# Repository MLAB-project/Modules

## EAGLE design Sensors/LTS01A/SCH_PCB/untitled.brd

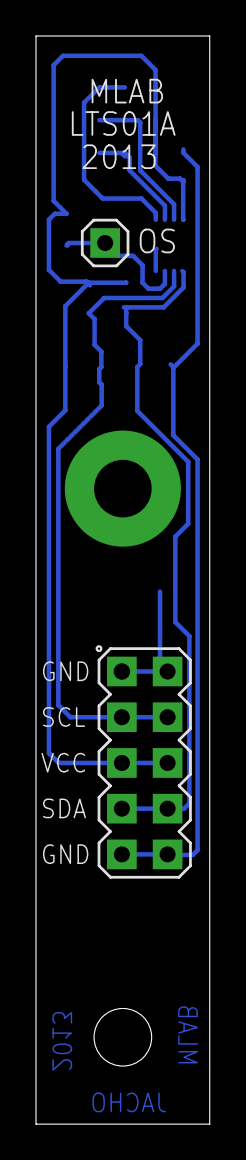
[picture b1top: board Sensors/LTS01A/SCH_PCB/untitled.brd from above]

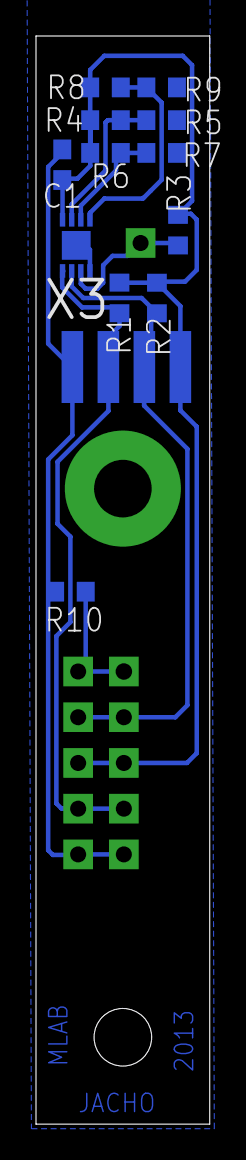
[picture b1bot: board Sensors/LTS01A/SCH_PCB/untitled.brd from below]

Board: 2 copper layers, 9.7 x 60.5 mm, 16 parts (13 on the bottom side), 9 nets.

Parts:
C1: 100nF; C0603
R1, R2, R3: 10k; R0603
R4, R5, R6, R7, R8, R9, R10: 0R; R0603
SV1: MA05-2
SV2: SMD_MA04-1
SV4: MA01-1
X2: SROUB3M
X3: TDFN8

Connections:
A0: R4.2, R5.1, X3.7
A1: R6.2, R7.1, X3.6
A2: R8.2, R9.1, X3.5
GND: C1.2, R5.2, R7.2, R9.2, R10.2, SV1.9, SV1.10, SV2.4, X3.4, X3.9
unnamed: R10.1, SV1.1, SV1.2
OS: R3.1, SV4.1, X3.3
SCL: R2.1, SV1.3, SV1.4, SV2.2, X3.2
SDA: R1.1, SV1.7, SV1.8, SV2.3, X3.1
VCC: C1.1, R1.2, R2.2, R3.2, R4.1, R6.1, R8.1, SV1.5, SV1.6, SV2.1, X3.8

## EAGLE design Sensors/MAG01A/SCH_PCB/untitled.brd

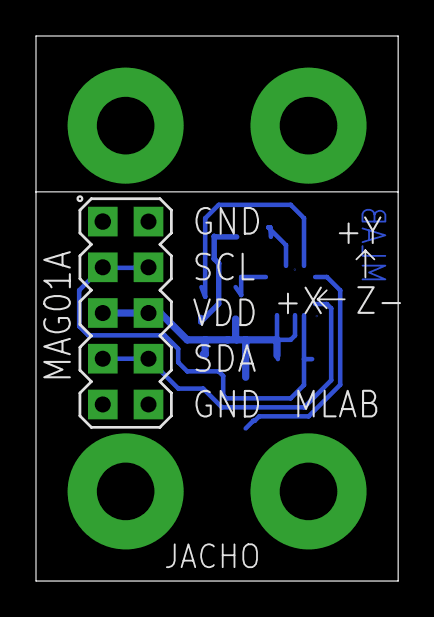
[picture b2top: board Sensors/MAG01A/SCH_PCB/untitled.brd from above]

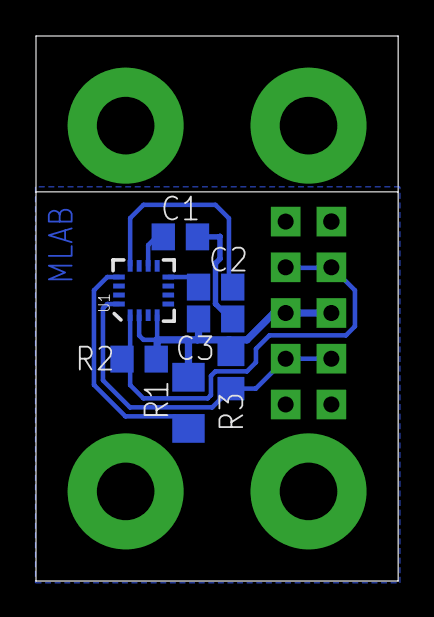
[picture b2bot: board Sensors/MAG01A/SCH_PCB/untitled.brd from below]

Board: 2 copper layers, 20.1 x 30.3 mm, 12 parts (7 on the bottom side), 8 nets.

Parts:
C1: 4.7uF; C0805
C2: 0.22uF; C0805
C3: 0.1uF; C0805
R1: 0R; 1206
R2, R3: 2k7; 0805
SV1: MA05-2
U1: HMC5883LSMD; 16LPCC
X1, X2, X3, X4: SROUB3M

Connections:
GND: C1.2, C3.2, SV1.1, SV1.2, SV1.9, SV1.10, U1.9, U1.11
unnamed: C1.1, U1.10
unnamed: R1.1, U1.13
unnamed: C2.1, U1.8
unnamed: C2.2, U1.12
SCL: R2.1, SV1.3, SV1.4, U1.1
SDA: R3.1, SV1.7, SV1.8, U1.16
VDD: C3.1, R1.2, R2.2, R3.2, SV1.5, SV1.6, U1.2, U1.4

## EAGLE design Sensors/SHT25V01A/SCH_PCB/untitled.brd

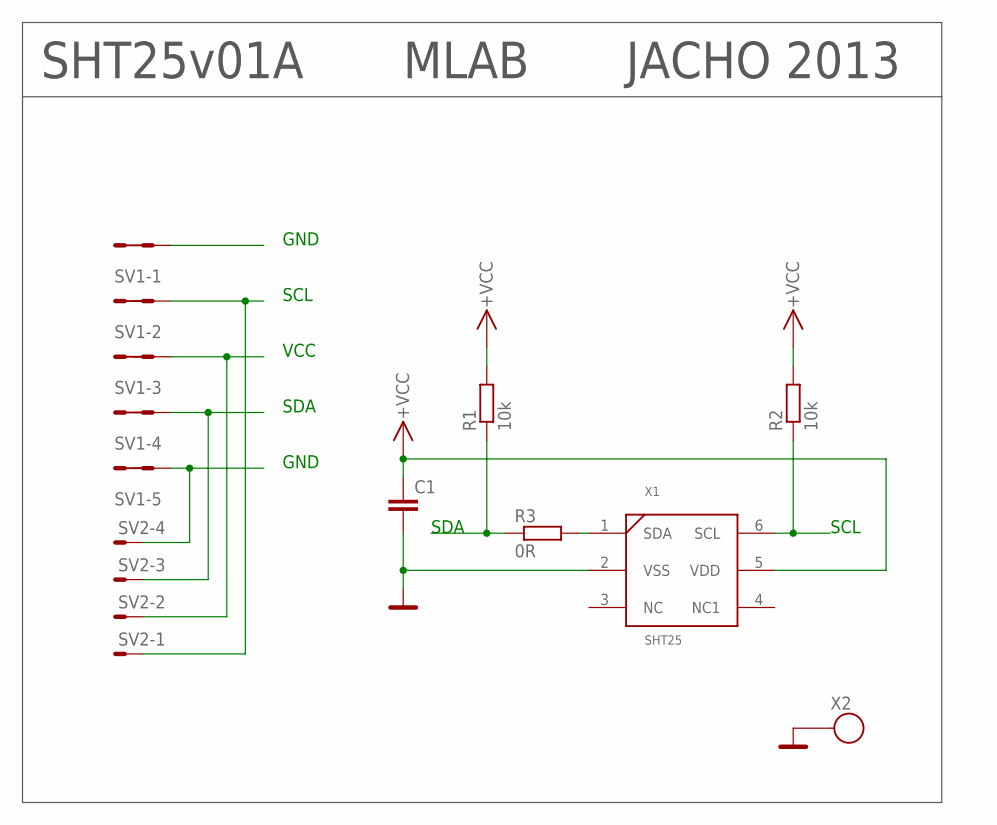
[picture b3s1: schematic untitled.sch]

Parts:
C1: C-EUC0603; C0603
R1, R2: 10k; R0603
R3: 0R; R0603
SV1: MA05-2
SV2: SMD_MA04-01; SMD_MA04-1
X1: SHT25
X2: SROUB3M

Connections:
GND: C1.2, SV1.1, SV1.2, SV1.9, SV1.10, SV2.4, X1.2 (VSS), X2.P$1; also elsewhere on the board
unnamed: R3.2, X1.1 (SDA)
SCL: R2.1, SV1.3, SV1.4, SV2.1, X1.6 (SCL)
SDA: R1.1, R3.1, SV1.7, SV1.8, SV2.3
VCC: C1.1, R1.2, R2.2, SV1.5, SV1.6, SV2.2, X1.5 (VDD); also elsewhere on the board

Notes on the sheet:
VCC
GND
SCL
SDA
SHT25v01A
MLAB
JACHO 2013

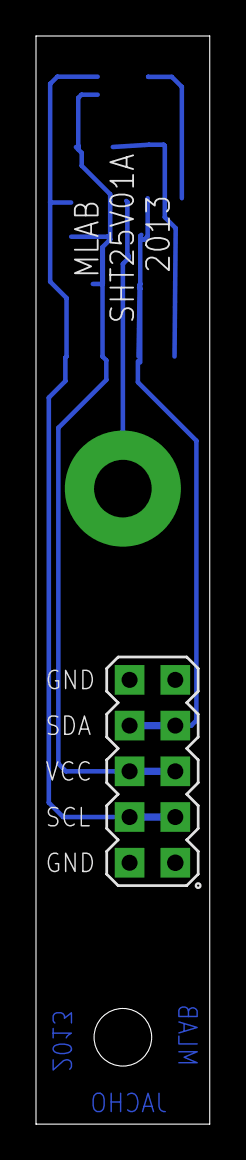
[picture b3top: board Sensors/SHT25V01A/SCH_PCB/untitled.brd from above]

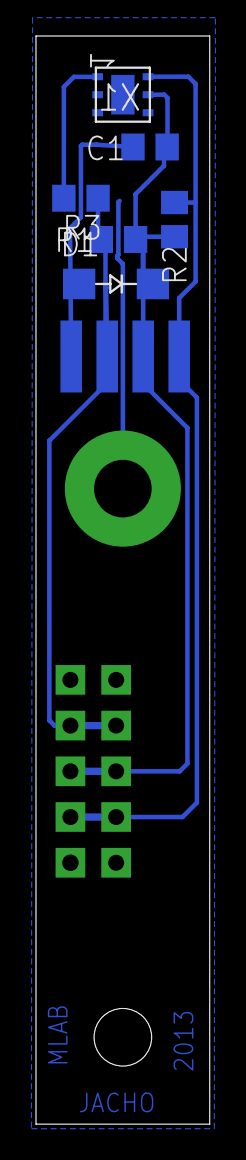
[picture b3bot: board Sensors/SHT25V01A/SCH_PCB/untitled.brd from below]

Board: 2 copper layers, 9.7 x 60.5 mm, 9 parts (7 on the bottom side), 5 nets.

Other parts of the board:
D1: SMA

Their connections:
GND: D1.A; also elsewhere on the board
VCC: D1.K; also elsewhere on the board

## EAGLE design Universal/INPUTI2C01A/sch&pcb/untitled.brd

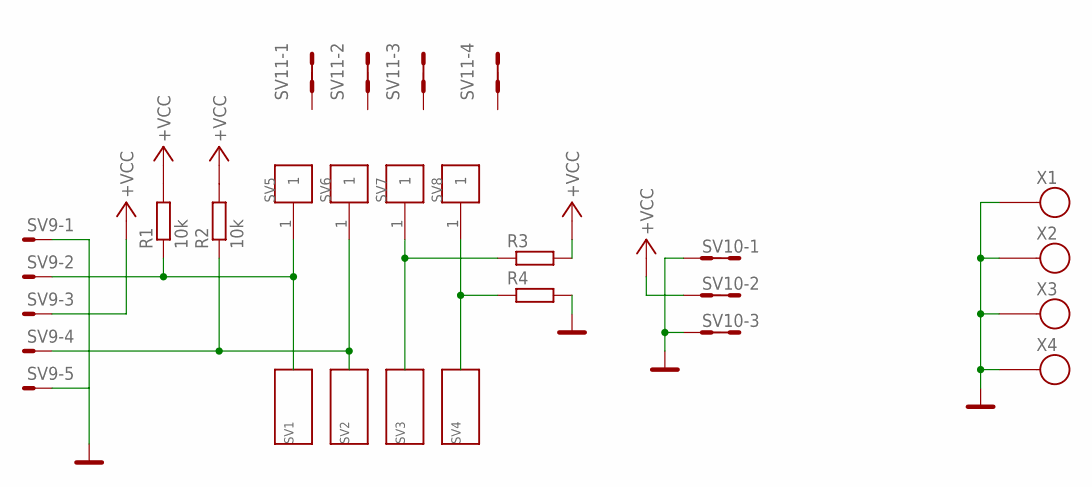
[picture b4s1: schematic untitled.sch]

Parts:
R1, R2: 10k; 0805
R3, R4: R0805; 0805
SV1, SV2, SV3, SV4: WAGO256
SV5, SV6, SV7, SV8: SMD:MA01-01; SMD_MA01-1
SV9: MA05-1
SV10: MA03-2
SV11: MA04-2
X1, X2, X3, X4: SROUB3M

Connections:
+VCC: R1.2, R2.2, R3.2, SV9.3, SV10.3, SV10.4
GND: R4.2, SV9.1, SV9.5, SV10.1, SV10.2, SV10.5, SV10.6, X1.P$1, X2.P$1, X3.P$1, X4.P$1
unnamed: R3.1, SV3.1, SV3.A1, SV7.1
unnamed: R1.1, SV1.1, SV1.A1, SV5.1, SV9.2
unnamed: R2.1, SV2.1, SV2.A1, SV6.1, SV9.4
unnamed: R4.1, SV4.1, SV4.A1, SV8.1

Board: 2 copper layers, 19 parts (0 on the bottom side), 6 nets, no tracks yet.

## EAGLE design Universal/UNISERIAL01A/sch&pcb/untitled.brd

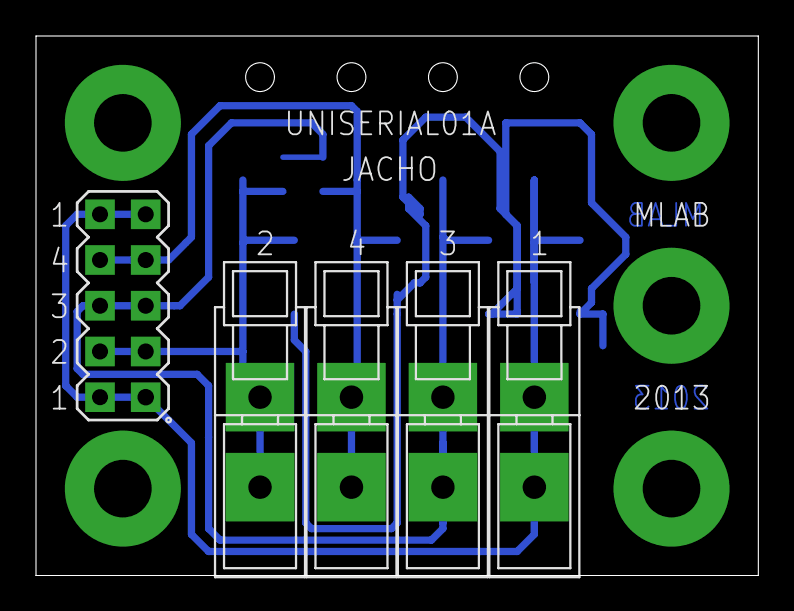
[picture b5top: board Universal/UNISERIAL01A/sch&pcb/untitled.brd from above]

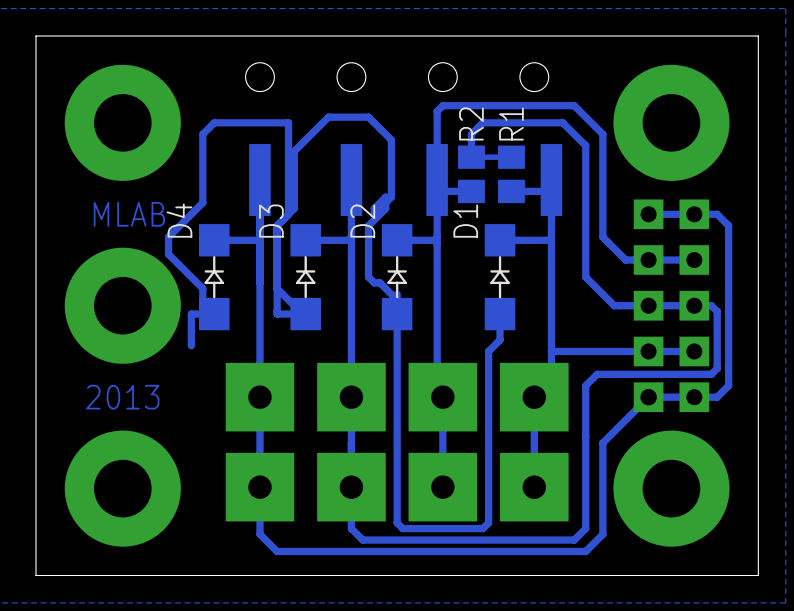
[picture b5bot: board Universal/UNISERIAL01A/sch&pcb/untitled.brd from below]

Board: 2 copper layers, 40.1 x 30.0 mm, 20 parts (10 on the bottom side), 5 nets.

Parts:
D1, D2, D3, D4: SMA
R1, R2: 10k; 0805
SV1, SV2, SV3, SV4: WAGO256
SV5, SV6, SV7, SV8: SMD_MA01-1
SV9: MA05-2
X1, X2, X3, X4, X5: SROUB3M

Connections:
+VCC: D3.K, R1.2, R2.2, SV3.1, SV3.A1, SV7.1, SV9.5, SV9.6
GND: D1.A, D2.A, D3.A, D4.A, X1.P$1, X2.P$1, X3.P$1, X4.P$1, X5.P$1
unnamed: D1.K, R1.1, SV1.1, SV1.A1, SV5.1, SV9.3, SV9.4
unnamed: D2.K, R2.1, SV2.1, SV2.A1, SV6.1, SV9.7, SV9.8
unnamed: D4.K, SV4.1, SV4.A1, SV8.1, SV9.1, SV9.2, SV9.9, SV9.10

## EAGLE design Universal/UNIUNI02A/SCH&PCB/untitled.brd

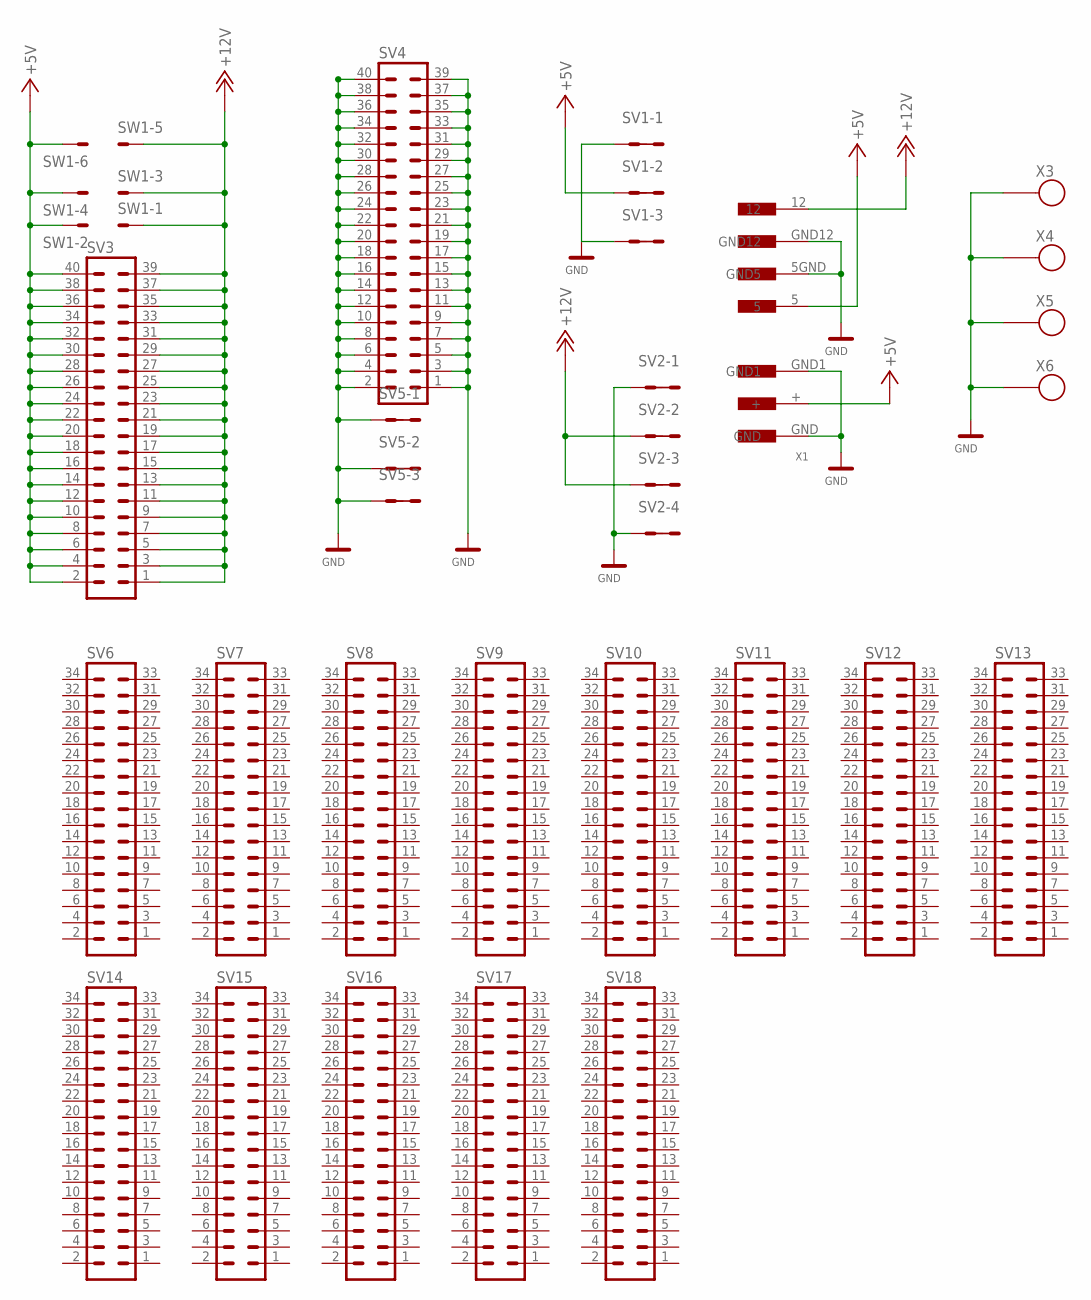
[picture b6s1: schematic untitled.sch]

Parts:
SV1, SV5: MA03-2
SV2: MA04-2
SV3, SV4: MA20-2
SV6, SV7, SV8, SV9, SV10, SV11, SV12, SV13, SV14, SV15, SV16, SV17, SV18: MA17-2
SW1: MA03-3; MA03-2
X1: KONEKTOR_DC_2.1MM
X2: POWER_HDD
X3, X4, X5, X6: SROUB3M

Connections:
+5V: SV1.3, SV1.4, SV3.2, SV3.4, SV3.6, SV3.8, SV3.10, SV3.12, SV3.14, SV3.16, SV3.18, SV3.20, SV3.22, SV3.24, SV3.26, SV3.28, SV3.30, SV3.32, SV3.34, SV3.36, SV3.38, SV3.40, SW1.2, SW1.4, SW1.6, X1.+, X2.5
+12V: SV2.3, SV2.4, SV2.5, SV2.6, SV3.1, SV3.3, SV3.5, SV3.7, SV3.9, SV3.11, SV3.13, SV3.15, SV3.17, SV3.19, SV3.21, SV3.23, SV3.25, SV3.27, SV3.29, SV3.31, SV3.33, SV3.35, SV3.37, SV3.39, SW1.1, SW1.3, SW1.5, X2.12
GND: SV1.1, SV1.2, SV1.5, SV1.6, SV2.1, SV2.2, SV2.7, SV2.8, SV4.1, SV4.2, SV4.3, SV4.4, SV4.5, SV4.6, SV4.7, SV4.8, SV4.9, SV4.10, SV4.11, SV4.12, SV4.13, SV4.14, SV4.15, SV4.16, SV4.17, SV4.18, SV4.19, SV4.20, SV4.21, SV4.22, SV4.23, SV4.24, SV4.25, SV4.26, SV4.27, SV4.28, SV4.29, SV4.30, SV4.31, SV4.32, SV4.33, SV4.34, SV4.35, SV4.36, SV4.37, SV4.38, SV4.39, SV4.40, SV5.1, SV5.2, SV5.3, SV5.4, SV5.5, SV5.6, X1.GND, X1.GND1, X2.5GND (GND5), X2.GND12, X3.P$1, X4.P$1, X5.P$1, X6.P$1

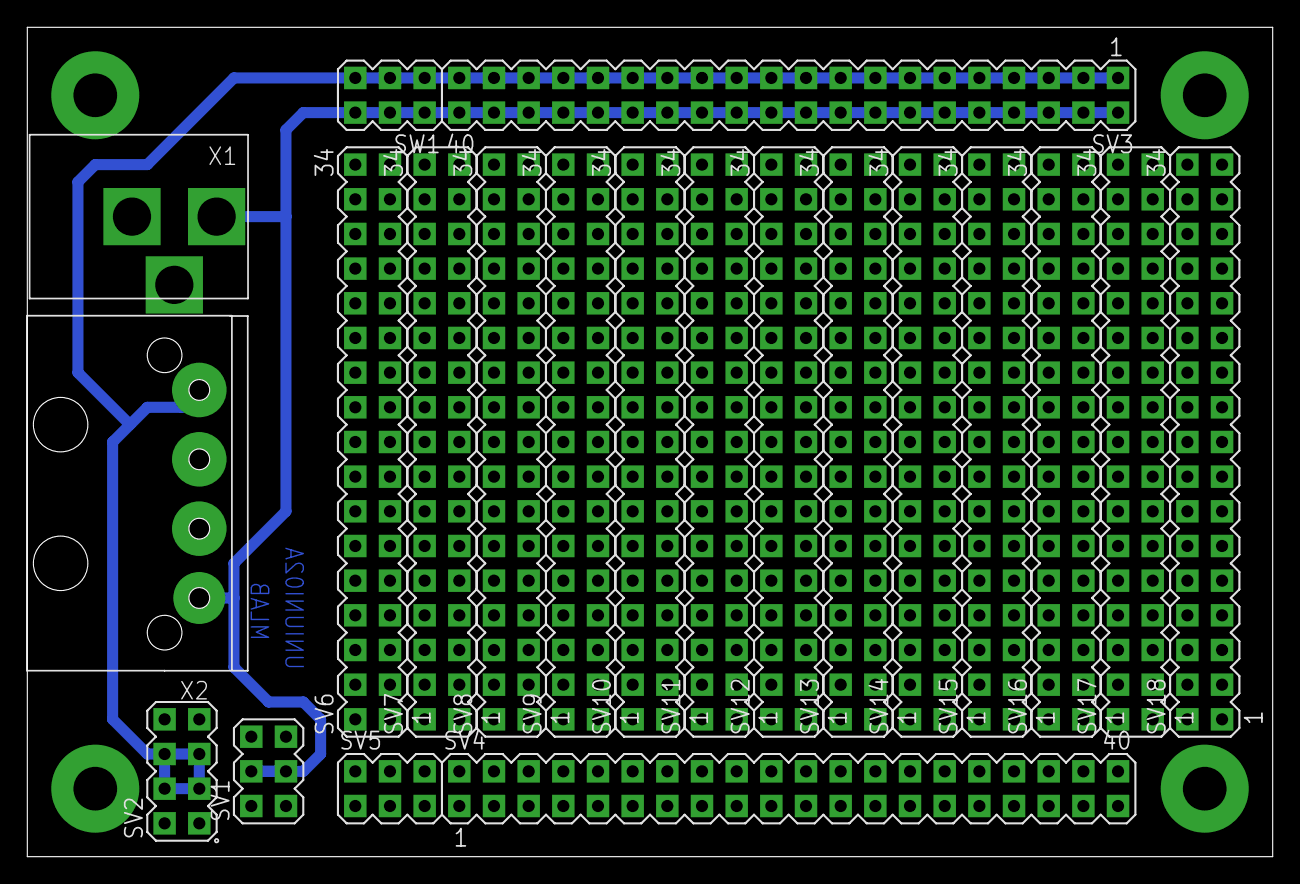
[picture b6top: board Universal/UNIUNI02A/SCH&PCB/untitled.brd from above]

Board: 2 copper layers, 91.2 x 60.8 mm, 25 parts (0 on the bottom side), 3 nets.

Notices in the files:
parts and their libraries:
PaJa_22: Copyright (C) PaJa 2001-2010
